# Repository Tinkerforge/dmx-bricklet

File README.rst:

DMX Bricklet
============

This repository contains the firmware source code and the hardware design
files. The documentation generator configs can be found at
https://github.com/Tinkerforge/generators

Repository Content
------------------

software/:
 * examples/: Examples for all supported languages
 * build/: Compiled files
 * src/: Source code of firmware
 * Makefile: Makefile to build project

hardware/:
 * Contains KiCad project files and additionally schematics as PDF

datasheets/:
 * Contains datasheets for sensors and complex ICs that are used

Hardware
--------

The hardware is designed with the open source EDA Suite KiCad
(http://www.kicad.org). Before you are able to open the files,
you have to install the Tinkerforge kicad-libraries
(https://github.com/Tinkerforge/kicad-libraries). You can either clone
them directly in hardware/ or clone them in a separate folder and
symlink them into hardware/
(ln -s kicad_path/kicad-libraries project_path/hardware). After that you
can open the .pro file in hardware/ with KiCad and from there view and
modify the schematics and the PCB layout.

Software
--------

If you want to do your own Brick/Bricklet firmware development we highly
recommend that you use our build environment setup script and read the
tutorial (https://www.tinkerforge.com/en/doc/Tutorials/Tutorial_Build_Environment/Tutorial.html).

To compile the C code we recommend you to install the newest GNU Arm Embedded
Toolchain (https://launchpad.net/gcc-arm-embedded/+download).
You also need to install bricklib2 (https://github.com/Tinkerforge/bricklib2).

You can either clone it directly in software/src/ or clone it in a
separate folder and symlink it into software/src/
(ln -s bricklib_path/bricklib2 project_path/software/src/). Finally make sure to
have CMake installed (http://www.cmake.org/cmake/resources/software.html).

After that you can build the firmware by invoking make in software/.
The firmware (.zbin) can then be found in software/build/ and uploaded
with brickv (click button "Flashing" on start screen).

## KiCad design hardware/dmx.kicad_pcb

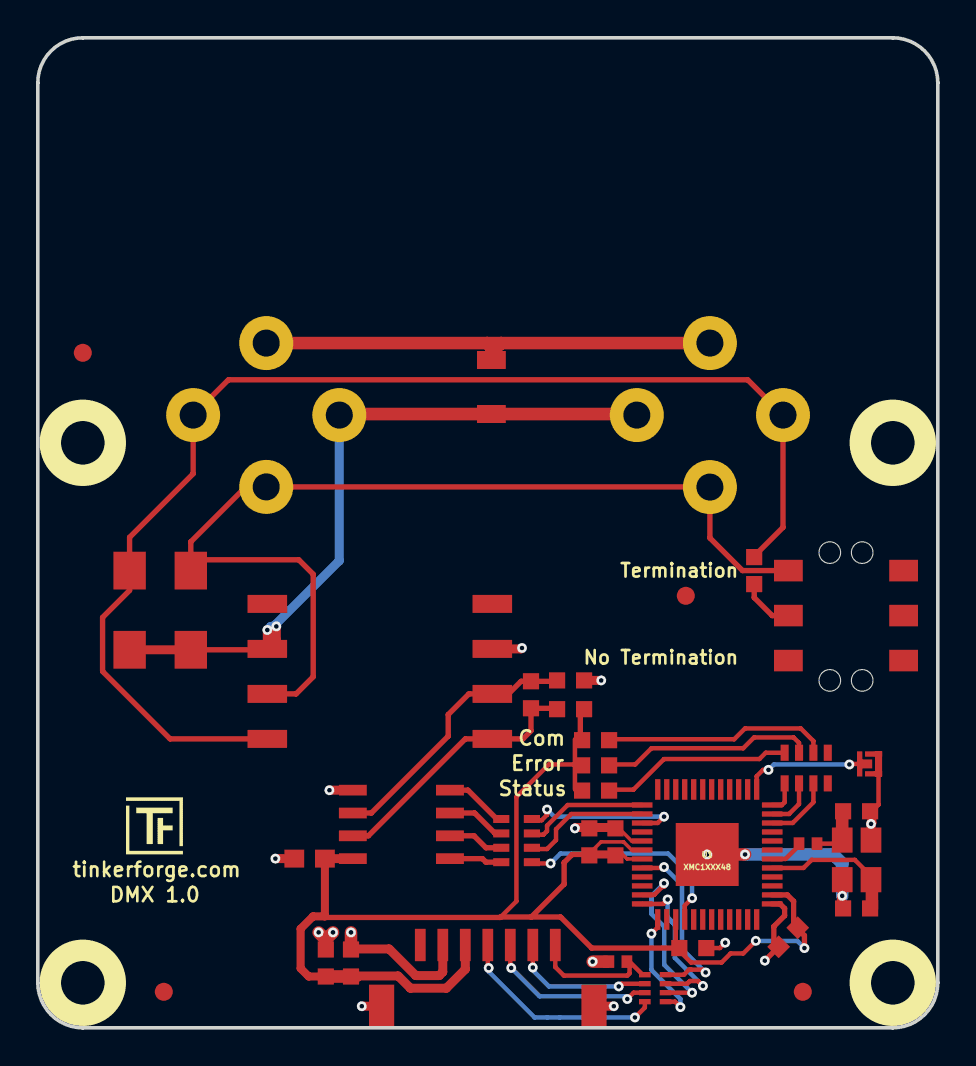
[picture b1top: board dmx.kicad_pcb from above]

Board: 2 copper layers, 50.0 x 55.0 mm, 41 parts (0 on the bottom side), 35 nets.

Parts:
C1, C2: 1uF; C0603F
C3, C4, C5: 100nF; C0603F
C6: 220nF; C0603F
C7: 100nF; C0603E
C8, C9: 10pF; C0603F
C10: 220pF; C0402F
D1: yellow; D0603F
D2: red; D0603F
D3: blue; D0603F
D4, D5: SMAJ24CA; DO-214AC
Fiducial_Mark: VAL**; Fiducial_Mark
Fiducial_Mark#2, Fiducial_Mark#3, Fiducial_Mark#4: VAL**; Fiducial_Mark
L1: WE-SL
P1: CON-SENSOR2
P2: BOOT; SolderJumper
P3: DMXCON_2x3; DMX_IN_OUT_2x3POL
R1: 120; R0603F
R2: DNP; R1206
R3, R5: 10k; R0603F
R4: 2.2k; R0603F
R9: 0; R0402F
RP1: 1k; 0603X4
RP2: 10k; 0603X4
RP4: 82; 4X0402
SW1: TER; SLIDE_SWITCH
U1: XMC1XXX48; QFN48-EP2
U2, U3, U4, U5: DRILL; DRILL_NP
U6: ADM3485; SOIC8
VAL: CE_5mm
X1: 16MHz; CRYSTAL_3225

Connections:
485-DE: RP2.3, U1.13
485-RX: RP2.1, U1.28
485-TX: RP2.4, U1.15
485-~RE: RP2.2, U1.14
GND: C1.1, C2.1, C3.2, C4.2, C5.2, C6.2, C7.1, C8.2, C9.2, C10.2, L1.3, P1.2, P1.EP, P2.1, R5.2, U1.17, U1.37, U1.EP, U6.5, X1.3
unnamed: C8.1, U1.41, X1.2
unnamed: C9.1, R9.2, X1.1
unnamed: C10.1, P1.7, RP4.5
unnamed: D1.2, RP1.2
unnamed: D2.2, RP1.3
unnamed: D3.2, RP1.4
unnamed: D4.1, L1.7, P3.3, P3.6, SW1.1
unnamed: D4.2, D5.2, L1.6, P3.1, P3.4, R2.2
unnamed: D5.1, L1.8, P3.2, P3.5, R1.2
unnamed: L1.1, R3.2, R4.1, U6.7
unnamed: L1.2, R4.2, R5.1, U6.6
unnamed: P1.4, RP4.8
unnamed: P1.5, RP4.7
unnamed: P1.6, RP4.6
unnamed: P2.2, U1.1
unnamed: P3.7, P3.8, R2.1
unnamed: R1.1, SW1.2
unnamed: R9.1, U1.42
unnamed: RP1.5, U1.48
unnamed: RP1.6, U1.47
unnamed: RP1.7, U1.46
unnamed: RP2.5, U6.4
unnamed: RP2.6, U6.3
unnamed: RP2.7, U6.2
unnamed: RP2.8, U6.1
S-CLK: RP4.2, U1.23
S-CS: RP4.1, U1.25
S-MISO: RP4.4, U1.20
S-MOSI: RP4.3, U1.24
VCC: C1.2, C2.2, C3.1, C4.1, C5.1, C6.1, C7.2, D1.1, D2.1, D3.1, P1.3, R3.1, U1.18, U1.19, U1.27, U1.38, U6.8

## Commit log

2017-02-15 Initial check in
2017-02-15 Add schematic
2017-02-16 Change transreciever IC to ADM3485 (half-duplex)
2017-02-17 Add PCB layout
2017-02-17 Remove PTC1
2017-02-20 Add WEEE and CE logos
2017-03-01 Fix CE logo
2017-05-05 Change filtering to R/C circuit
2017-05-05 Add schematic PDF
2017-05-05 Remove RP3
2017-06-09 Add .gitignore
2017-06-09 Add initial stub firmware implementation
2017-06-20 change rx pin connection to p3.0
2017-06-20 drc check
2017-06-21 Add initial DMX Master and Slave implementation
    TODO: * Remove LED debug
    * Fix rare crash during mode change
    * Improve interrupt performance
    * Test with Master Brick under load
2017-06-21 Remove debug
2017-06-21 Rename parity in framing error
2017-06-21 Increase frame number each frame
2017-06-21 Reinitialize DMX/RS485 data during mode change
2017-06-21 Remove prototype code (pin 2_13 is not connected in production board)
2017-08-10 hardware changes
    * increase board size to 60x50mm
    * add fiducials
    * fix all footprints with silkscreen layers
    * fix routing after moving connector
2017-08-10 add 3d model for slide switch
2017-08-11 add shielded dmx connector footprint, specify filter
2017-08-24 Fix edge cuts; specify R9 to 0Ohm
2017-11-06 Add final schematic
2017-11-09 Fix LED colors in 3d model
2017-11-09 Add 3d model (*.step & *.FCStd)
2017-11-16 Remove bogus draw frame function
2017-11-16 add termination switch silkscreen description
2017-11-20 Add .step file instead of .net file
2017-11-21 Remove WIP maker
2017-11-21 Rename file
2017-11-23 Unificate file names
2018-02-20 Cleanup KiCad libraries config
    Ensure LibDir=kicad-libraries and LibName1=tinkerforge.
    Remove special library.
2018-03-05 Remove unused flash-size define
2018-06-18 Change capacitor footprint(s) to C0402F
2018-06-28 Fix readme
2018-07-11 Add Makefile with docker support
2018-07-11 Update directory structure and build instructions
2018-07-11 Remove obsolete generate_makefile scripts
2018-10-04 Increase version for new release (changes in bricklib2)
2018-10-04 Add rev to changelog
2018-11-12 Add simple DMX Bricklet example
2018-11-28 c: Add missing stream length parameter
2018-12-14 Add go examples.
2018-12-18 go: Change import path.
2018-12-18 go: Change import path again.
2018-12-20 rust: Fix result variable names in examples.
2019-01-24 mqtt: Add examples.
2019-01-24 mqtt: Fix example header.
2019-01-24 mqtt: Remove executable bit in example permissions.
2019-01-24 go: Minor example fixes.
2019-01-24 mqtt: Minor example fixes.
2019-03-28 mqtt: Fix whitespace.
2019-03-28 c: Examples: Pre-declare array used as parameter.
2019-05-14 Update rust examples.
2019-11-21 Add 4us wait-time between slots (some DMX slaves can not handle 0us wait time)
2019-11-21 Add ref for 2.0.3
2020-01-13 examples: Use python3 input instead of python2 raw_input.
2020-01-13 examples: mqtt: Remove trailing whitespace.
2020-03-16 Whitespace
2020-04-03 Add openHAB examples.
2020-04-07 examples: rust: Always block when calling bindings functions.
2020-08-19 Add uc examples.
2020-08-25 uc: Fix whitespace
2020-08-27 uc: Fix warnings.
2020-09-02 uc: Add example driver note.
2021-10-25 Update KiCad link
    https://www.kicad.org/blog/2021/10/Avoid-links-to-former-kicad-domain/
2022-04-19 examples: uc: Rename TF_HalContext to TF_HAL.
2022-04-27 uc: Adapt to bindings changes
2022-05-04 javascript: Add callback example to continuously write a value
2022-07-06 Add license files.
2025-10-04 Fix compatibility with new Docker build image (GCC 14.2.1)

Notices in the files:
hardware/dmx.kicad_pcb:
Licensed under CERN OHL v.1.1
Copyright (©) 2016, L.Lauer
